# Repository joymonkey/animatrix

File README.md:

# animatrix

**animatrix** is an open-source hardware, firmware, and software toolkit for custom LED matrix displays.

The project began as a reproduction display for a Daft Punk helmet visor (a 40×3 matrix sitting across the visor opening), but is designed to be hardware- and geometry-agnostic over time to support a variety of custom LED matrix projects.

## Hardware
KiCad design files for the custom flexible PCB LED matrix
- **EDA Tool:** KiCad 10
- **Matrix:** 40 columns × 3 rows (120 LEDs total) on a 2-layer flexible printed circuit (FPC).
- **LEDs:** Standard 3mm (T-1) through-hole LEDs spaced on a 6.0 mm grid pitch.
- **Driver:** Lumissil / ISSI **IS31FL3731**, communicating over I2C with per-pixel 8-bit PWM brightness control.
- **Interface:** Controller tail designed to mate directly with a Waveshare ESP32-S3 Zero.

## Firmware
ESP32-S3 firmware to drive the matrix and play animations
- **Platform:** ESP32-S3 using PlatformIO and the Arduino core.
- **Architecture:**
  - **Core 0 (Networking & Control):** Wi-Fi (SoftAP/Station), AsyncWebServer, REST API, and LittleFS file management.
  - **Core 1 (Animation Engine):** Real-time frame playback and I2C communication with the IS31FL3731 driver.
- **Animation Format:** Interprets lightweight JSON animation files.
- **UI & Control Options:**
  - **Web UI:** Hosted onboard over Wi-Fi (SoftAP/Station) for smartphone/browser control, animation triggering, and file uploads.
  - **Physical Triggers:** Support for external hardware pushbuttons (e.g., wearable/costume triggers), directly wired on via a separate device using ESP-Now.

## Website
Animatrix LED Studio companion web app for creating animations. Preview it at https://joymonkey.github.io/animatrix/
  - Visual editor with frame-by-frame drawing tools and LED bloom/visor simulation.
  - Multi-frame timeline sequencer with undo/redo and variable frame rates.
  - Procedural generators: Cylon/KITT sweeps, robotic eye gestures, audio spectrum visualizers, breathing pulses, and text marquees. All of which can be mixed together into single animations.
  - Multi-track timeline compositing (additive, max, overwrite, and screen blend modes).
  - Export to JSON, C++ PROGMEM headers (Arduino / ESP-IDF), or direct over-the-air HTTP upload to the ESP32-S3.

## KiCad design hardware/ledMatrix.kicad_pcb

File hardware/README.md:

# animatrix — Hardware

This directory contains KiCad 10 design files for a custom 40×3 (120 LEDs total) flexible circuit board (FPC) using standard 3mm through-hole LEDs spaced on a 6.0 mm grid. The display is driven by a Lumissil IS31FL3731 charlieplexing driver IC (SSOP-28) over I2C with individual 8-bit PWM brightness control, powered via 5V USB VBUS, and featuring a direct-solder controller tail designed to interface with a Waveshare ESP32-S3 Zero.

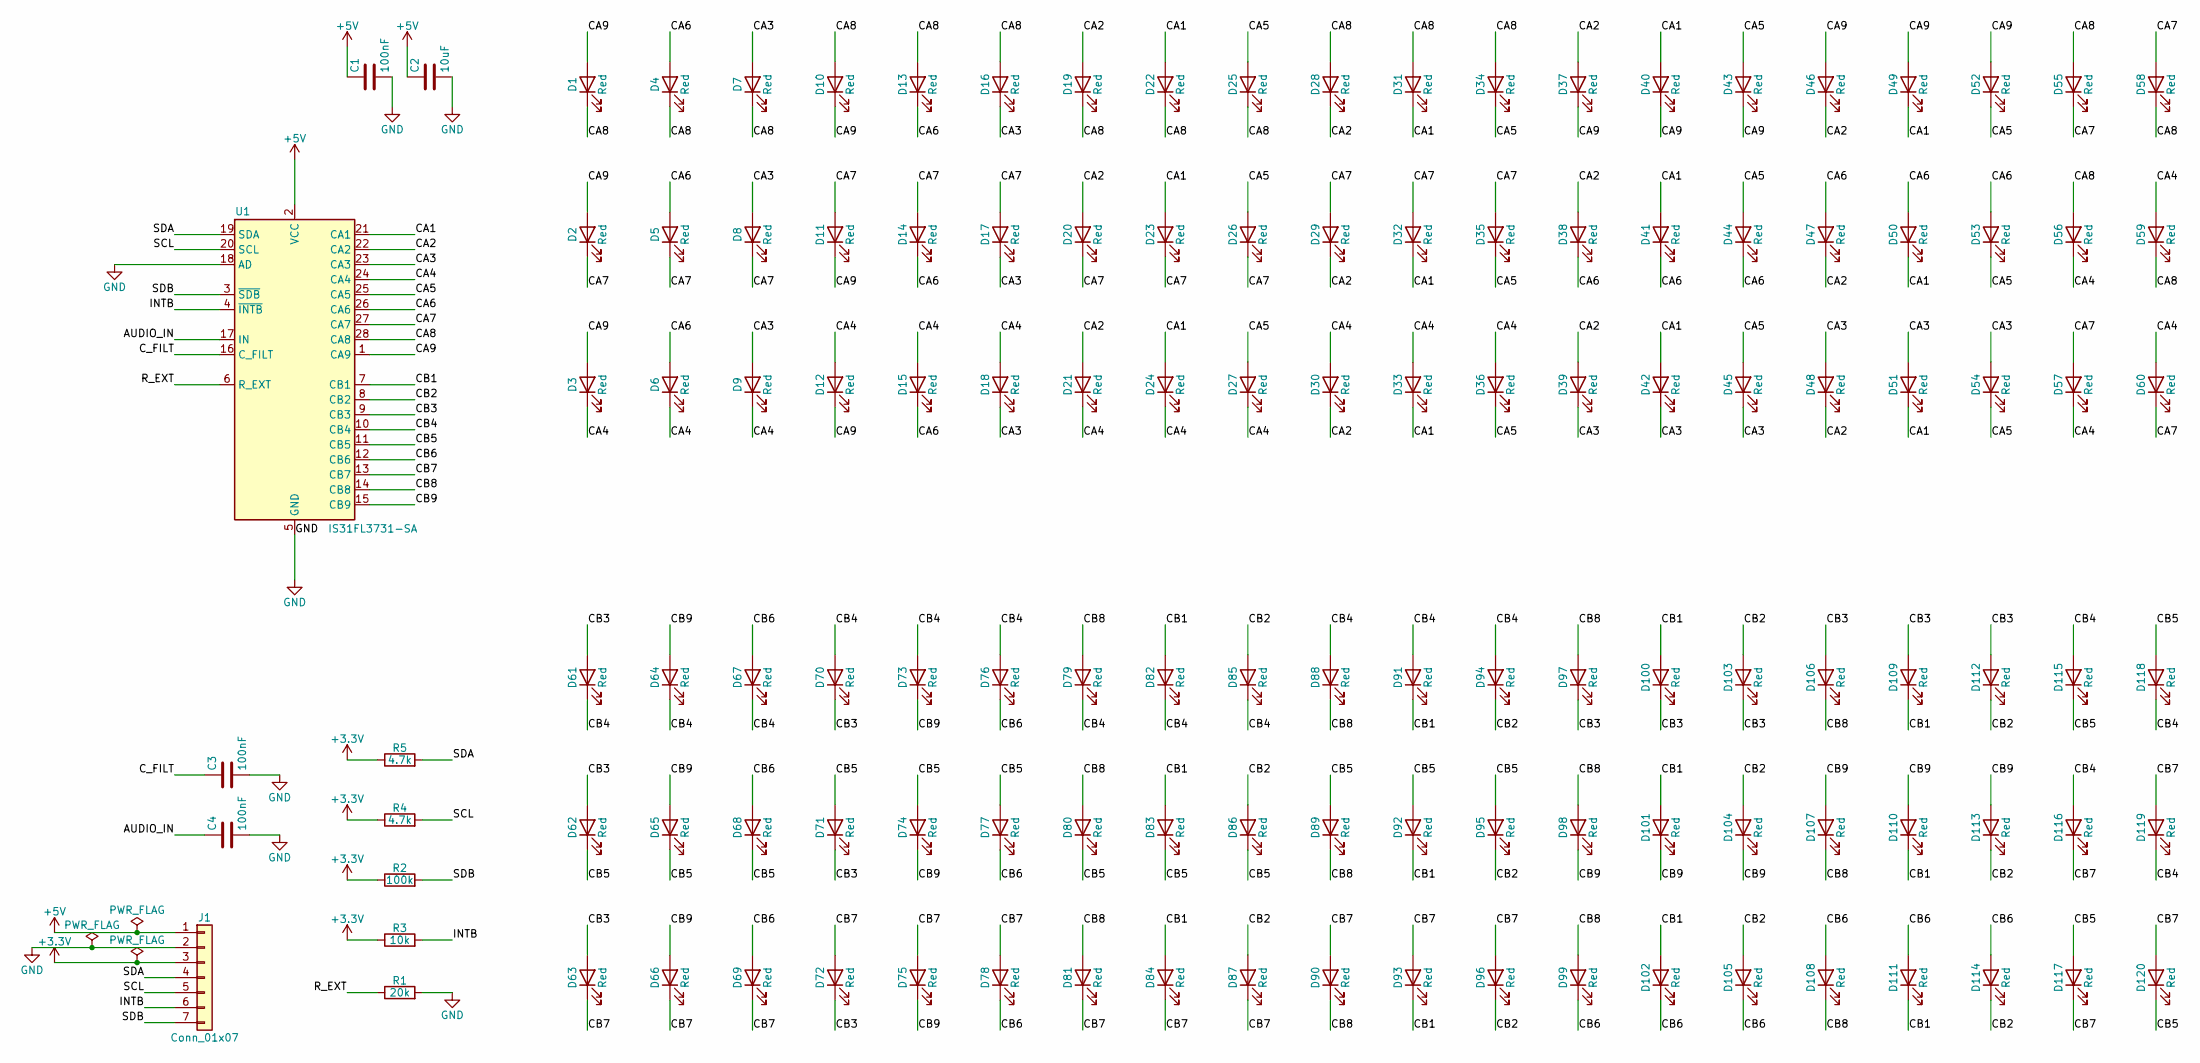
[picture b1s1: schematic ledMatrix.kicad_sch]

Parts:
C1, C3, C4: 100nF; C_0805_2012Metric
C2: 10uF; C_0805_2012Metric
D1, D2, D3, D4, D5, D6, D7, D8, D9, D10, D11, D12, D13, D14, D15, D16, D17, D18, D19, D20, D21, D22, D23, D24, D25, D26, D27, D28, D29, D30, D31, D32, D33, D34, D35, D36, D37, D38, D39, D40, D41, D42, D43, D44, D45, D46, D47, D48, D49, D50, D51, D52, D53, D54, D55, D56, D57, D58, D59, D60, D61, D62, D63, D64, D65, D66, D67, D68, D69, D70, D71, D72, D73, D74, D75, D76, D77, D78, D79, D80, D81, D82, D83, D84, D85, D86, D87, D88, D89, D90, D91, D92, D93, D94, D95, D96, D97, D98, D99, D100, D101, D102, D103, D104, D105, D106, D107, D108, D109, D110, D111, D112, D113, D114, D115, D116, D117, D118, D119, D120: Red; LED_D3.0mm
J1: Conn_01x07; PinHeader_1x07_P2.54mm_Vertical
R1: 20k; R_0805_2012Metric
R2: 100k; R_0805_2012Metric
R3: 10k; R_0805_2012Metric
R4, R5: 4.7k; R_0805_2012Metric
U1: IS31FL3731-SA; SSOP-28_5.3x10.2mm_P0.65mm

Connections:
+3.3V: J1.3, R2.1, R3.1, R4.1, R5.1
+5V: C1.1, C2.1, J1.1, U1.2 (VCC)
/AUDIO_IN: C4.1, U1.17 (IN)
/CA1: D22.2 (A), D23.2 (A), D24.2 (A), D31.1 (K), D32.1 (K), D33.1 (K), D40.2 (A), D41.2 (A), D42.2 (A), D49.1 (K), D50.1 (K), D51.1 (K), U1.21 (CA1)
/CA2: D19.2 (A), D20.2 (A), D21.2 (A), D28.1 (K), D29.1 (K), D30.1 (K), D37.2 (A), D38.2 (A), D39.2 (A), D46.1 (K), D47.1 (K), D48.1 (K), U1.22 (CA2)
/CA3: D7.2 (A), D8.2 (A), D9.2 (A), D16.1 (K), D17.1 (K), D18.1 (K), D39.1 (K), D42.1 (K), D45.1 (K), D48.2 (A), D51.2 (A), D54.2 (A), U1.23 (CA3)
/CA4: D3.1 (K), D6.1 (K), D9.1 (K), D12.2 (A), D15.2 (A), D18.2 (A), D21.1 (K), D24.1 (K), D27.1 (K), D30.2 (A), D33.2 (A), D36.2 (A), D56.1 (K), D57.1 (K), D59.2 (A), D60.2 (A), U1.24 (CA4)
/CA5: D25.2 (A), D26.2 (A), D27.2 (A), D34.1 (K), D35.1 (K), D36.1 (K), D43.2 (A), D44.2 (A), D45.2 (A), D52.1 (K), D53.1 (K), D54.1 (K), U1.25 (CA5)
/CA6: D4.2 (A), D5.2 (A), D6.2 (A), D13.1 (K), D14.1 (K), D15.1 (K), D38.1 (K), D41.1 (K), D44.1 (K), D47.2 (A), D50.2 (A), D53.2 (A), U1.26 (CA6)
/CA7: D2.1 (K), D5.1 (K), D8.1 (K), D11.2 (A), D14.2 (A), D17.2 (A), D20.1 (K), D23.1 (K), D26.1 (K), D29.2 (A), D32.2 (A), D35.2 (A), D55.1 (K), D57.2 (A), D58.2 (A), D60.1 (K), U1.27 (CA7)
/CA8: D1.1 (K), D4.1 (K), D7.1 (K), D10.2 (A), D13.2 (A), D16.2 (A), D19.1 (K), D22.1 (K), D25.1 (K), D28.2 (A), D31.2 (A), D34.2 (A), D55.2 (A), D56.2 (A), D58.1 (K), D59.1 (K), U1.28 (CA8)
/CA9: D1.2 (A), D2.2 (A), D3.2 (A), D10.1 (K), D11.1 (K), D12.1 (K), D37.1 (K), D40.1 (K), D43.1 (K), D46.2 (A), D49.2 (A), D52.2 (A), U1.1 (CA9)
/CB1: D82.2 (A), D83.2 (A), D84.2 (A), D91.1 (K), D92.1 (K), D93.1 (K), D100.2 (A), D101.2 (A), D102.2 (A), D109.1 (K), D110.1 (K), D111.1 (K), U1.7 (CB1)
/CB2: D85.2 (A), D86.2 (A), D87.2 (A), D94.1 (K), D95.1 (K), D96.1 (K), D103.2 (A), D104.2 (A), D105.2 (A), D112.1 (K), D113.1 (K), D114.1 (K), U1.8 (CB2)
/CB3: D61.2 (A), D62.2 (A), D63.2 (A), D70.1 (K), D71.1 (K), D72.1 (K), D97.1 (K), D100.1 (K), D103.1 (K), D106.2 (A), D109.2 (A), D112.2 (A), U1.9 (CB3)
/CB4: D61.1 (K), D64.1 (K), D67.1 (K), D70.2 (A), D73.2 (A), D76.2 (A), D79.1 (K), D82.1 (K), D85.1 (K), D88.2 (A), D91.2 (A), D94.2 (A), D115.2 (A), D116.2 (A), D118.1 (K), D119.1 (K), U1.10 (CB4)
/CB5: D62.1 (K), D65.1 (K), D68.1 (K), D71.2 (A), D74.2 (A), D77.2 (A), D80.1 (K), D83.1 (K), D86.1 (K), D89.2 (A), D92.2 (A), D95.2 (A), D115.1 (K), D117.2 (A), D118.2 (A), D120.1 (K), U1.11 (CB5)
/CB6: D67.2 (A), D68.2 (A), D69.2 (A), D76.1 (K), D77.1 (K), D78.1 (K), D99.1 (K), D102.1 (K), D105.1 (K), D108.2 (A), D111.2 (A), D114.2 (A), U1.12 (CB6)
/CB7: D63.1 (K), D66.1 (K), D69.1 (K), D72.2 (A), D75.2 (A), D78.2 (A), D81.1 (K), D84.1 (K), D87.1 (K), D90.2 (A), D93.2 (A), D96.2 (A), D116.1 (K), D117.1 (K), D119.2 (A), D120.2 (A), U1.13 (CB7)
/CB8: D79.2 (A), D80.2 (A), D81.2 (A), D88.1 (K), D89.1 (K), D90.1 (K), D97.2 (A), D98.2 (A), D99.2 (A), D106.1 (K), D107.1 (K), D108.1 (K), U1.14 (CB8)
/CB9: D64.2 (A), D65.2 (A), D66.2 (A), D73.1 (K), D74.1 (K), D75.1 (K), D98.1 (K), D101.1 (K), D104.1 (K), D107.2 (A), D110.2 (A), D113.2 (A), U1.15 (CB9)
/C_FILT: C3.1, U1.16 (C_FILT)
/INTB: J1.6, R3.2, U1.4 (~INTB)
/R_EXT: R1.1, U1.6 (R_EXT)
/SCL: J1.5, R4.2, U1.20 (SCL)
/SDA: J1.4, R5.2, U1.19 (SDA)
/SDB: J1.7, R2.2, U1.3 (~SDB)
GND: C1.2, C2.2, C3.2, C4.2, J1.2, R1.2, U1.5 (GND), U1.18 (AD)

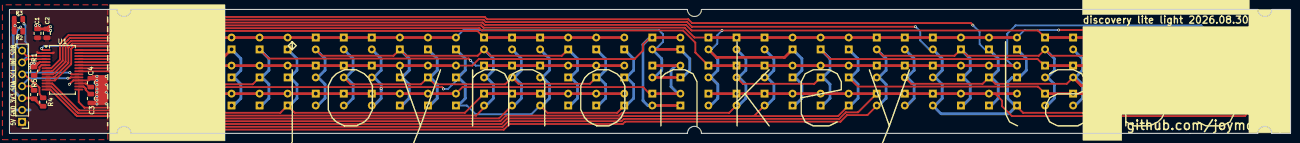
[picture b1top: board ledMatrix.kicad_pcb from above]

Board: 2 copper layers, 274.0 x 26.5 mm, 131 parts (0 on the bottom side), 28 nets.
